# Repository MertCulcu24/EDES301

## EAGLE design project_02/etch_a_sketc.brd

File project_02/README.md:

# Etch-a-Sketch PCB Project

## Project Overview
This project is a PCB design for an Etch-a-Sketch game using the PocketBeagle as the main processor. The design includes a custom PCB that connects the PocketBeagle to various components to create a functional electronic version of the classic Etch-a-Sketch toy.

## Features
- **SPI Display**: Shows the drawing created by the user
- **Dual Potentiometers**: Control horizontal and vertical movement
- **Push Buttons**: Reset the drawing and change colors
- **RGB LEDs**: Indicate the currently selected color
- **USB Port**: Provides power and potential connectivity for expansion

## Repository Structure
```
project_02/
├── EAGLE/
│   ├── etch_a_sketch.lbr  # Custom component library
│   ├── etch_a_sketch.sch  # Schematic design
│   └── etch_a_sketch.brd  # PCB layout
├── docs/
│   ├── mechanical_diagram.pdf  # Physical layout diagram
│   ├── top_layer_screenshot.png  # PCB top layer view
│   └── bottom_layer_screenshot.png  # PCB bottom layer view
├── MFG/
│   ├── etch_a_sketch_bom.csv  # Bill of Materials
│   └── [gerber files]  # Manufacturing files for PCB production
└── README.md 
```

## Design Specifications
- **Board Size**: 4" x 5" maximum
- **Layers**: 4-layer PCB design
- **Design Rules**:
  - Signal traces: 10 mil width / 10 mil spacing
  - Power/ground traces: 15 mil width / 15 mil spacing
  - Vias: 12 mil drill / 24 mil pad

## Component List
- PocketBeagle single-board computer
- 2.8" SPI TFT Display
- 2x 10kΩ potentiometers (for X and Y control)
- 2x push buttons (reset and color change)
- 3x LEDs (red, green, blue)
- USB connector
- Various resistors and supporting components

## How to Use
1. Assemble the PCB with all components listed in the BOM
2. Power the board via USB
3. Press the color button to change drawing color
4. Press the reset button to clear the screen

## Manufacturing
This PCB was designed to be manufactured using standard PCB fabrication processes. The Gerber files in the MFG folder can be sent to any PCB manufacturer for production.

## Course Information
- **Course**: EDES301 - PCB Design
- **Due Date**: May 6, 2025
- **Instructor**: Dr. Welsh

## License
All design files are provided for educational purposes.

## Contact
mc205@rice.edu

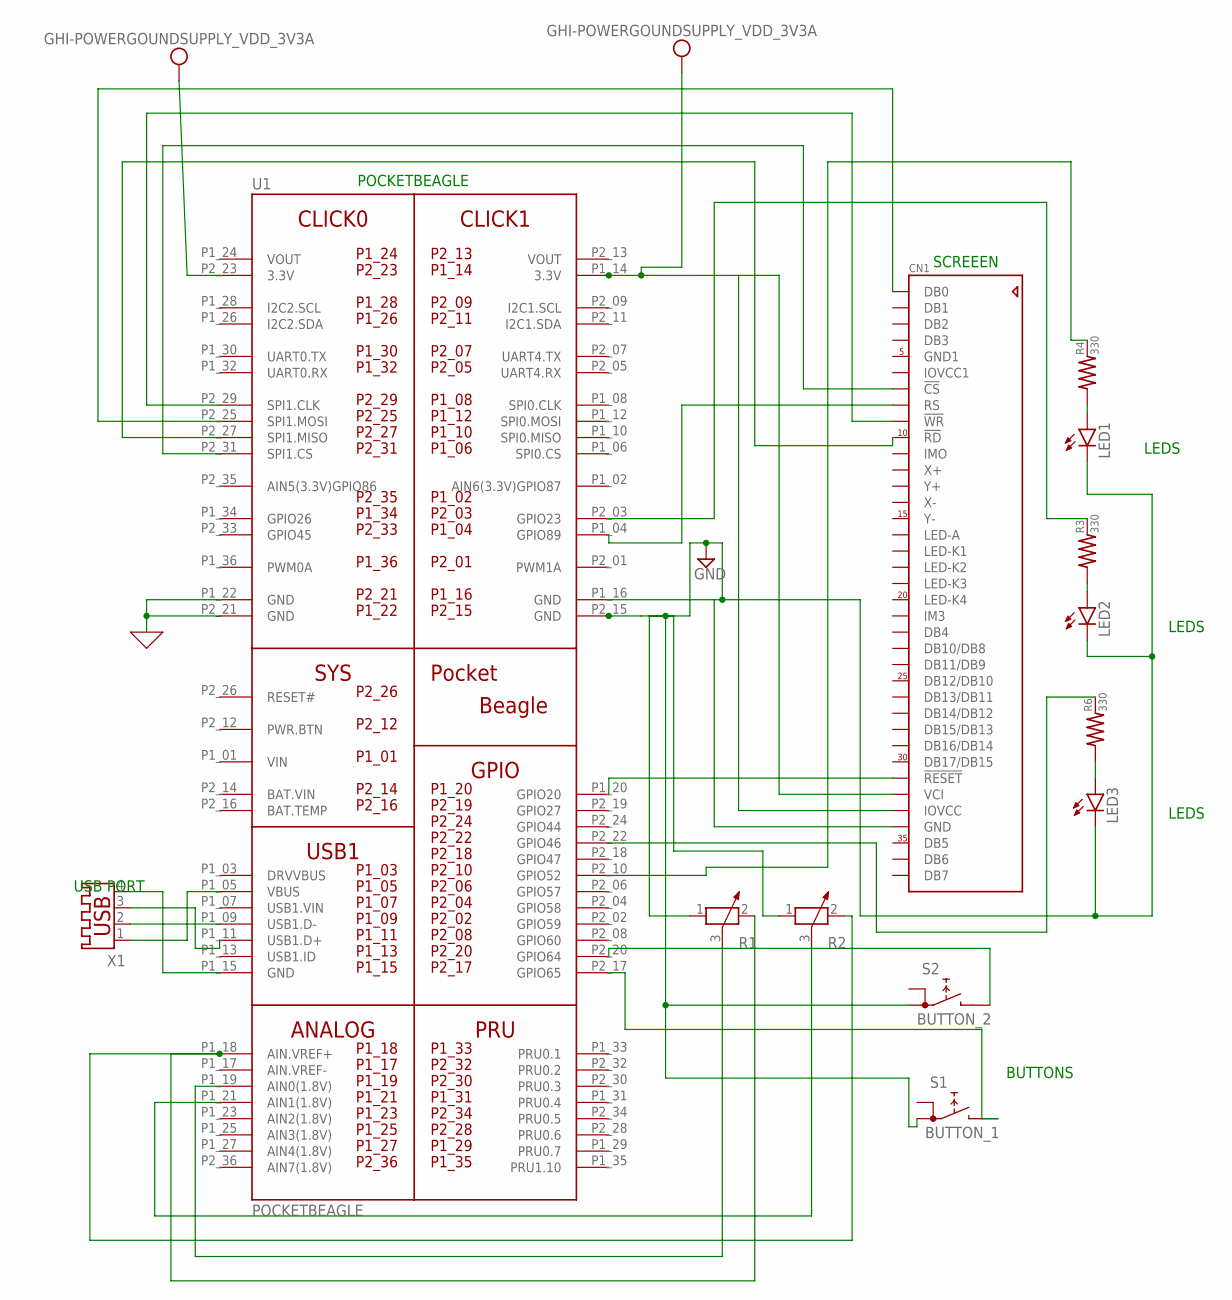
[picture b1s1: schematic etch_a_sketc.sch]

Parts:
CN1: ADAFRUIT_ILI9325_LCD1.0MM; ADAFRUIT_ILI9325_28INCH_TS
LED1: LED_BLUE5MM; LED5MM
LED2: LED_GREEN5MM; LED5MM
LED3: LED_RED5MM; LED5MM
R1: POTENTIOMETER_PT-10; PT-10
R2: POTENTIOMETER_2PT-10; PT-10
R3, R4, R6: 330; GHI-BASICCOMPONENTS_0402
S1: BUTTON_1; RDT1034
S2: BUTTON_2; RDT1034
U1: POCKETBEAGLE
X1: USB_CONNECTOR; USB-A003

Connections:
0: U1.P1_22 (GND), U1.P2_21 (GND)
BAT.VIN: U1.P2_14 (BAT.VIN)
GND: CN1.34 (GND), LED1.K (C), LED2.K (C), LED3.K (C), R1.1, R2.1, S1.A1, S2.A1, U1.P1_16 (GND), U1.P2_15 (GND)
GND1: CN1.5 (GND1)
IOVCC1: CN1.6 (IOVCC1)
unnamed: CN1.7 (!CS), U1.P2_31 (SPI1.CS)
unnamed: CN1.8 (RS), U1.P1_04 (GPIO89)
unnamed: CN1.9 (!WR), U1.P2_29 (SPI1.CLK)
unnamed: CN1.10 (!RD), U1.P2_27 (SPI1.MISO)
unnamed: CN1.1 (DB0), U1.P2_25 (SPI1.MOSI)
unnamed: CN1.31 (!RESET), U1.P1_20 (GPIO20)
unnamed: U1.P1_09 (USB1.D-), X1.2
unnamed: R1.2, R2.2, U1.P1_18 (AIN.VREF+)
unnamed: R1.3, U1.P1_19 (AIN0(1.8V))
unnamed: R2.3, U1.P1_21 (AIN1(1.8V))
unnamed: LED1.A, R4.1
unnamed: S2.B, U1.P2_20 (GPIO64)
unnamed: S1.B, U1.P2_17 (GPIO65)
unnamed: LED2.A, R3.1
unnamed: LED3.A, R6.1
unnamed: U1.P1_05 (VBUS), X1.1
unnamed: U1.P1_11 (USB1.D+), X1.3
unnamed: U1.P1_15 (GND), X1.4
unnamed: R6.2, U1.P2_22 (GPIO46)
unnamed: R3.2, U1.P2_03 (GPIO23)
unnamed: R4.2, U1.P2_10 (GPIO52)
VDD_3V3A: CN1.32 (VCI), CN1.33 (IOVCC), U1.P1_14 (3.3V), U1.P2_23 (3.3V)
VIN: U1.P1_01 (VIN)
VOUT: U1.P1_24 (VOUT), U1.P2_13 (VOUT)

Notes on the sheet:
POCKETBEAGLE
SCREEEN
USB PORT
BUTTONS
LEDS

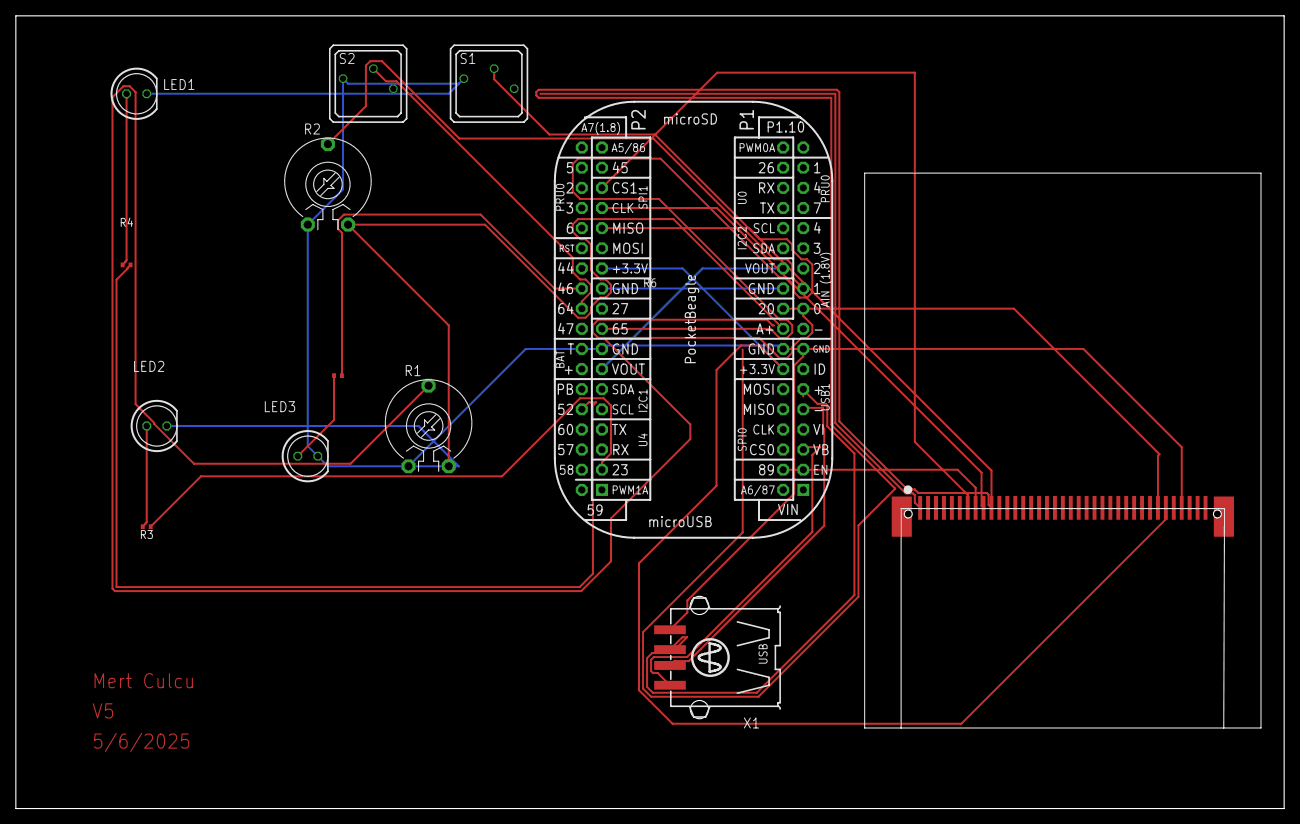
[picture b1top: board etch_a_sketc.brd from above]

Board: 4 copper layers, 160.0 x 100.0 mm, 13 parts (0 on the bottom side), 25 nets.

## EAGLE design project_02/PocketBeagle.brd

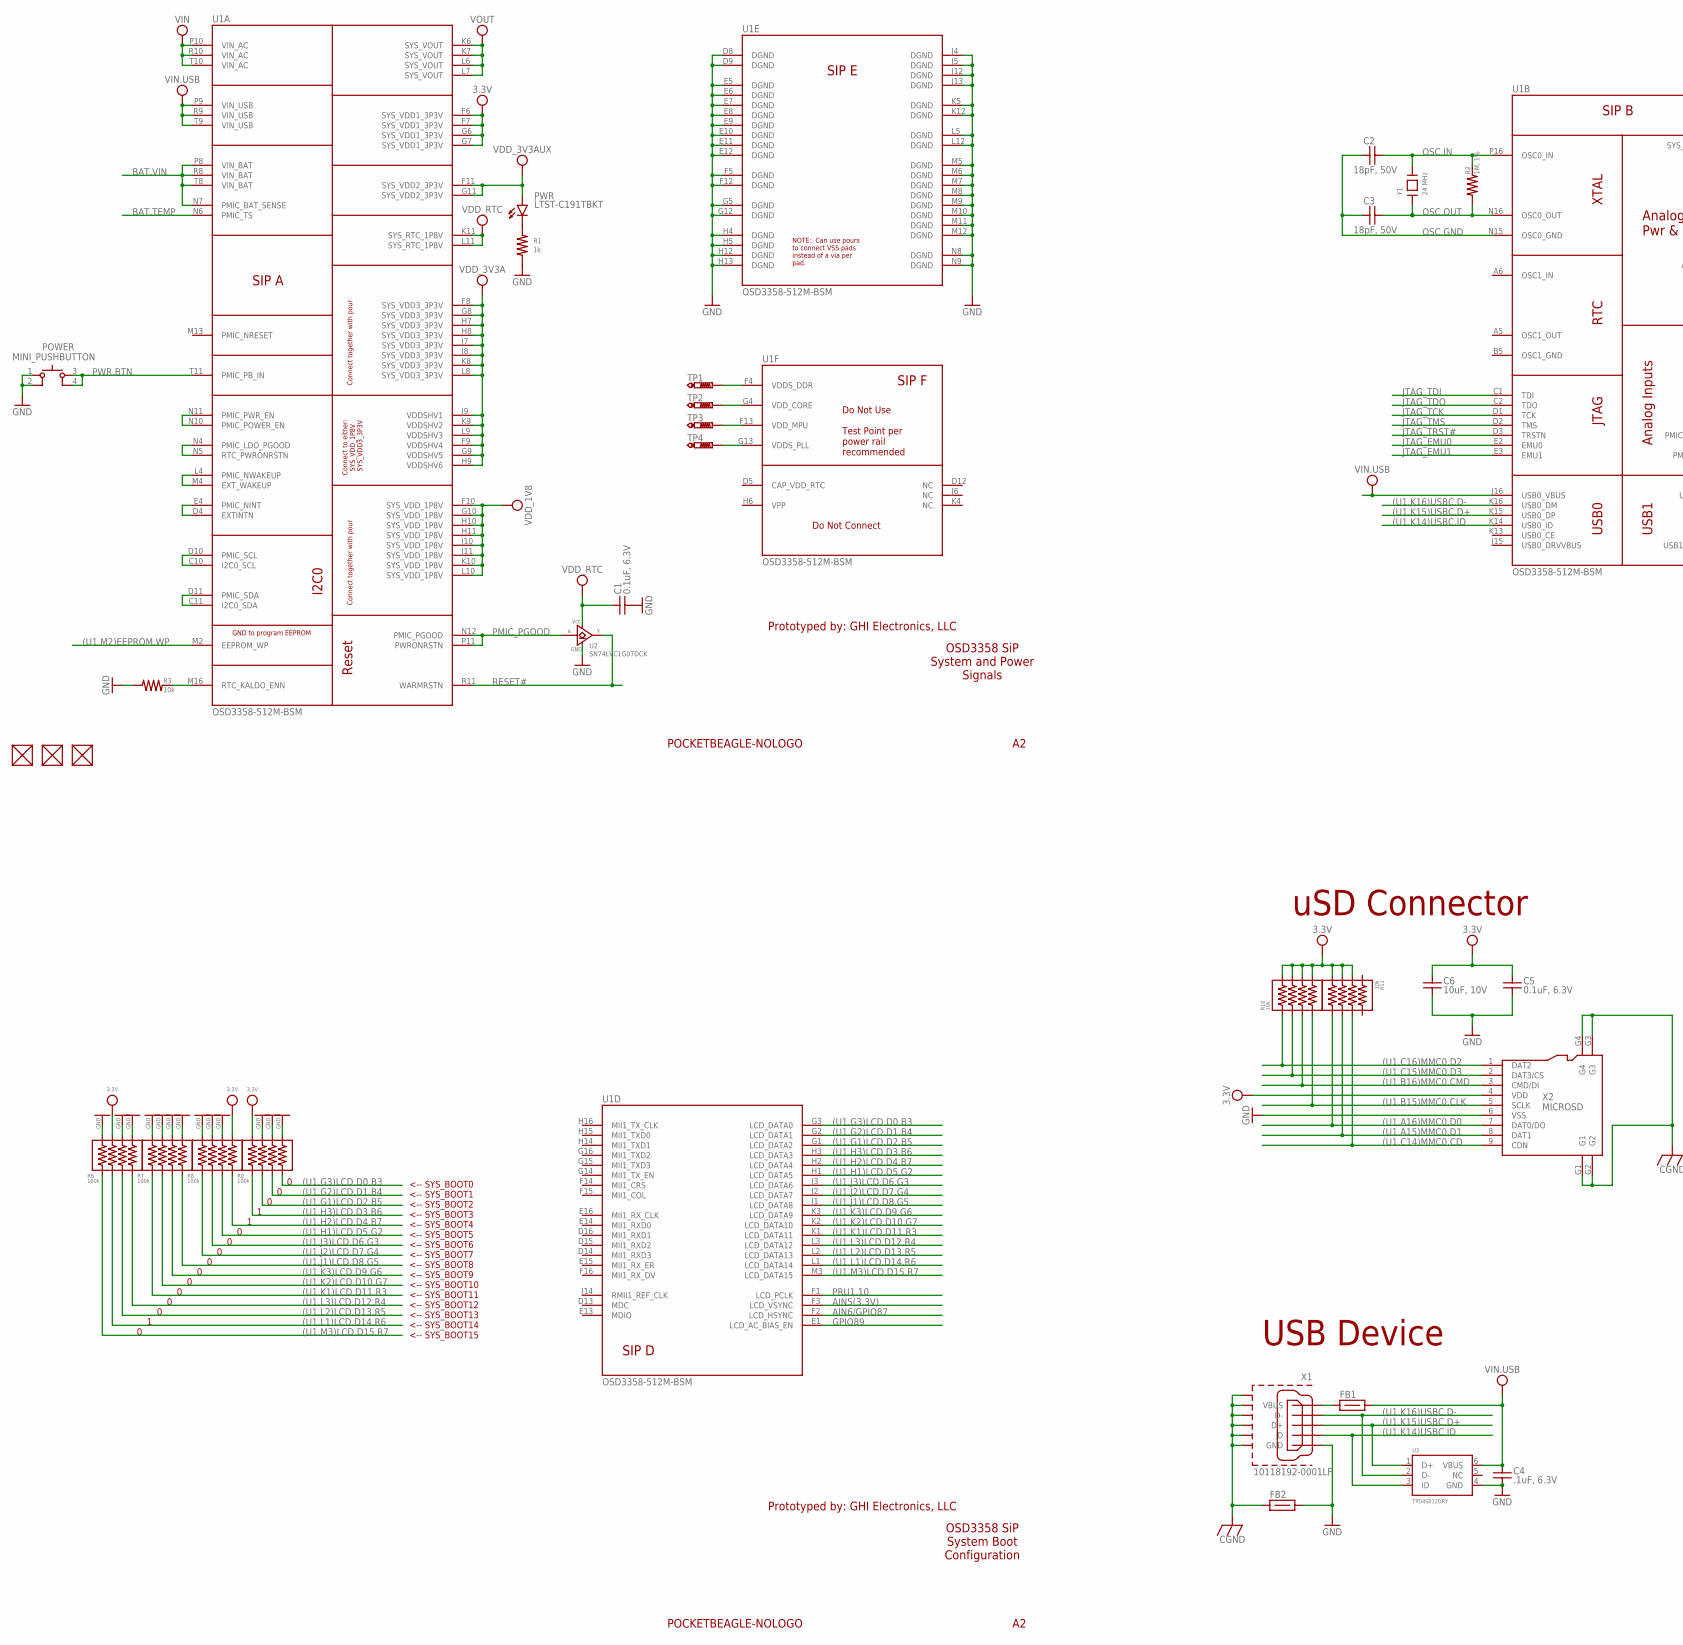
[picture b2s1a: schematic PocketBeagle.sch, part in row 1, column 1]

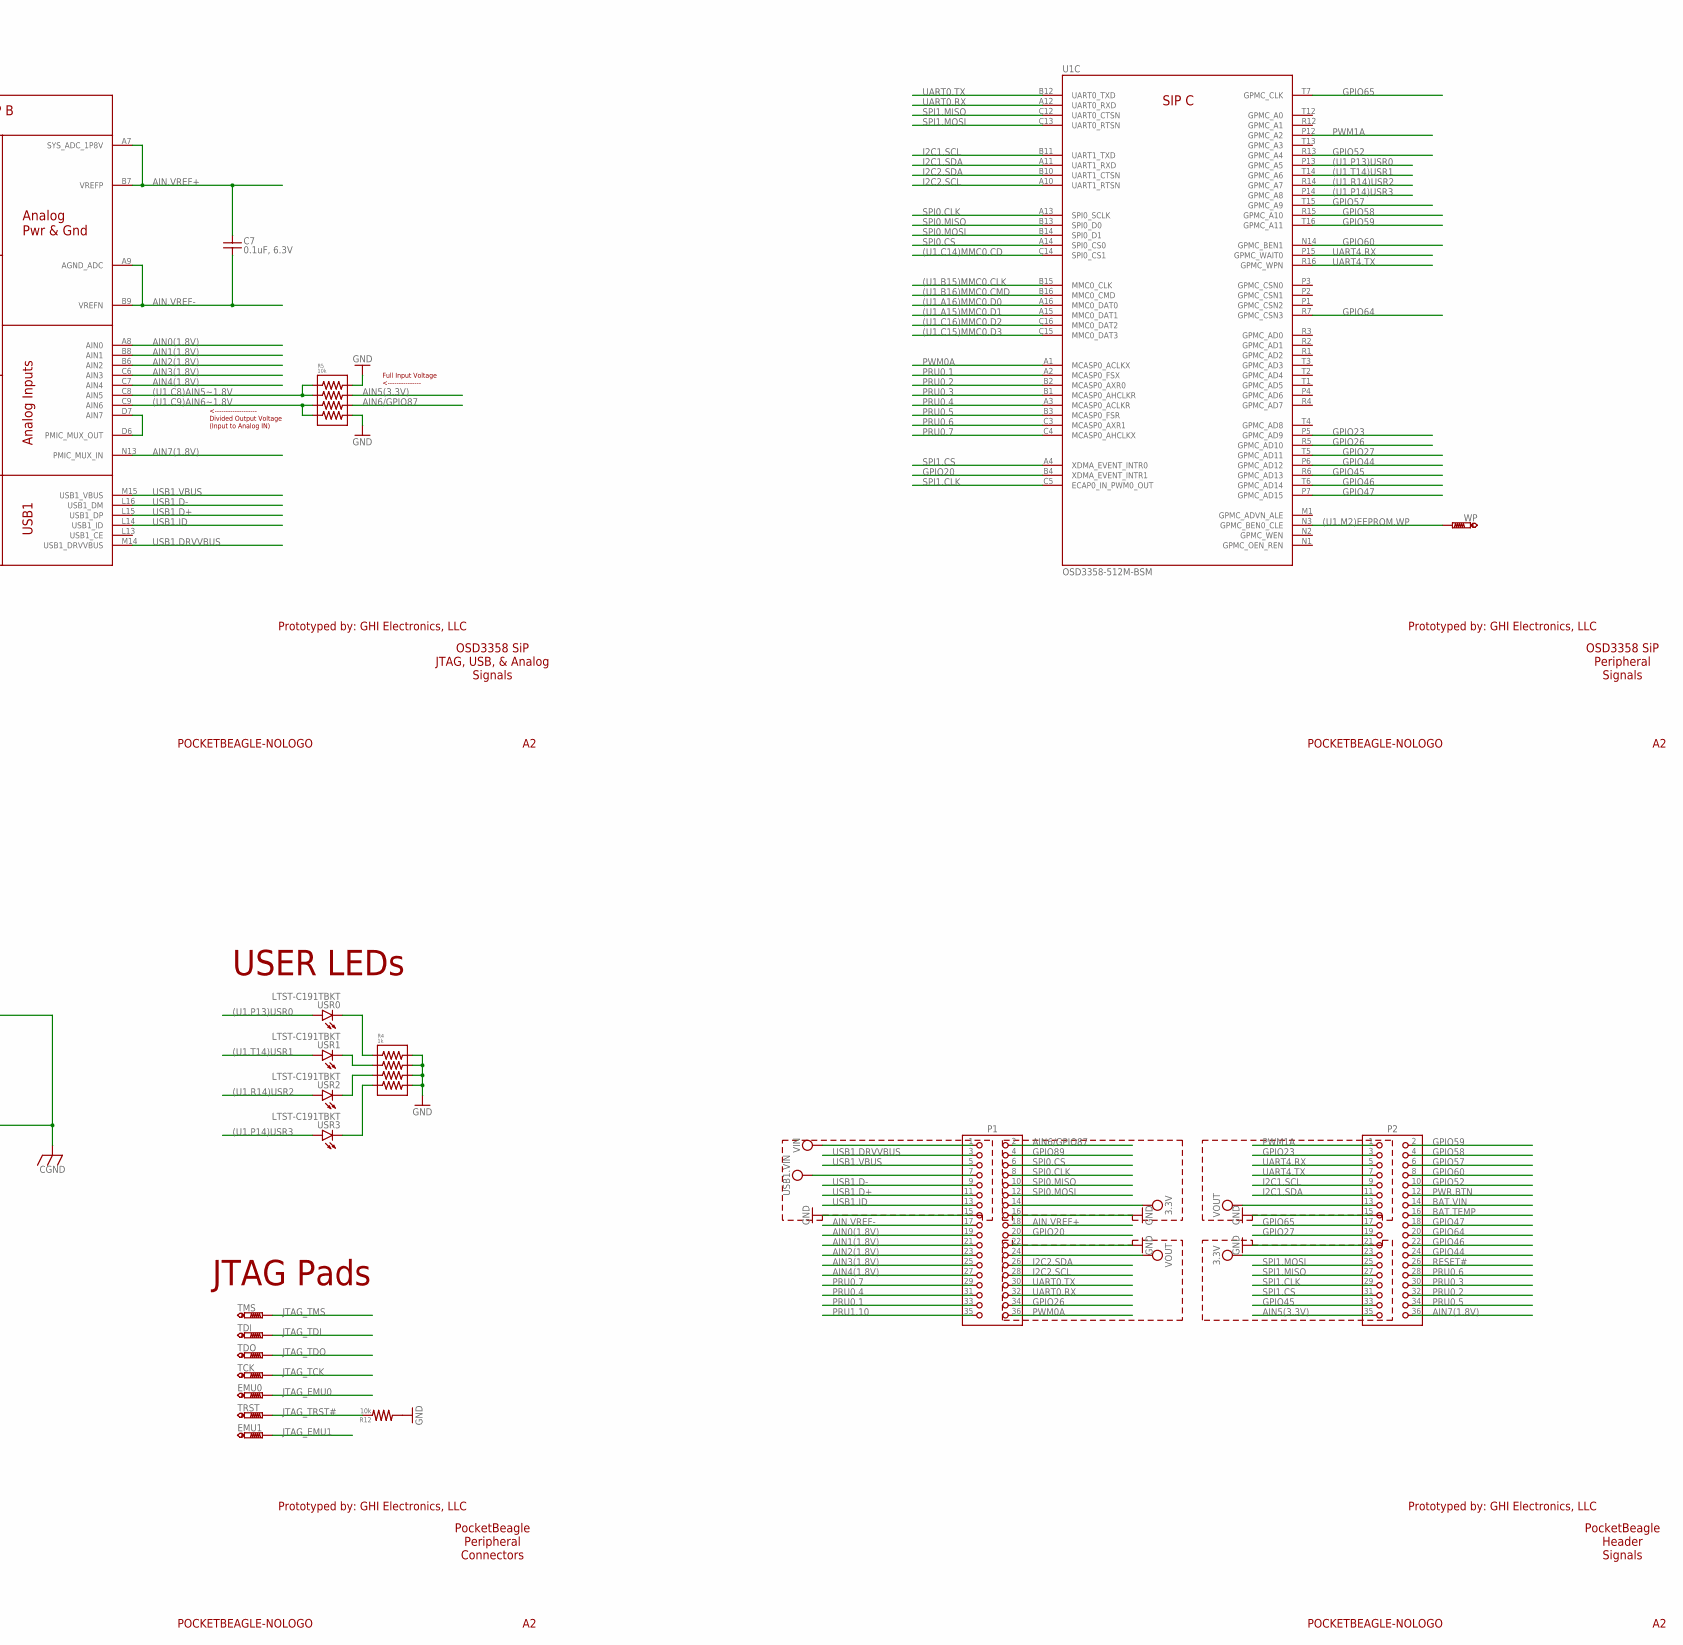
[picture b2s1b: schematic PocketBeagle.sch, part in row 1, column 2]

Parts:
C1, C5, C7: 0.1uF, 6.3V; 0402
C2, C3: 18pF, 50V; 0402
C4: .1uF, 6.3V; 0402
C6: 10uF, 10V; 0603
EMU0, EMU1: PTR1B1,27; B1,27
FB1, FB2: FB-(INCH)-0603; 0603
FUD1, FUD2, FUD3: FIDUCIAL; FIDUCIAL_40MIL
P1, P2: 2X18-(INCH)-0.1-TH-(35MIL-DIA)-W/O-SILK; TH-2X18-(35MIL-DIA)-W/O-SILK
POWER: MINI_PUSHBUTTON
PWR: LTST-C191TBKT; 0603-LED
R1: 1k; 0402
R2: 1M, 1%; 0402
R3, R12: 10k; 0402
R4: 1k; RN0804
R5, R10, R11: 10k; RN0804
R6, R7, R8, R9: 100k; RN0804
TCK: PTR1B1,27; B1,27
TDI: PTR1B1,27; B1,27
TDO: PTR1B1,27; B1,27
TMS: PTR1B1,27; B1,27
TP1, TP2, TP3, TP4: PTR1B1,27; B1,27
TRST: PTR1B1,27; B1,27
U1: OSD3358-512M-BSM; OSD335X-BGA-256
U2: SN74LVC1G07DCK; SC70(TI-DCK)
U3: TPD4S012DRY; SON-6(TI)-DRY
USR0, USR1, USR2, USR3: LTST-C191TBKT; 0603-LED
WP: PTR1B1,27; B1,27
X1: 10118192-0001LF; 10118192-0001LF(MICRO-USB-B-AMPHENOL-FCI)
X2: MICROSD
Y1: 24 MHz; CRYSTAL_5X3.2MM

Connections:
3.3V: C5.1, C6.1, P1.14, P2.23, R6.7, R8.5, R9.4, R10.5, R10.6, R10.7, R10.8, R11.2, R11.3, R11.4, U1.F6 (SYS_VDD1_3P3V), U1.F7 (SYS_VDD1_3P3V), U1.G6 (SYS_VDD1_3P3V), U1.G7 (SYS_VDD1_3P3V), X2.4 (VDD)
(U1.A15)MMC0.D1: R11.6, U1.A15 (MMC0_DAT1), X2.8 (DAT1)
(U1.A16)MMC0.D0: R11.5, U1.A16 (MMC0_DAT0), X2.7 (DAT0/DO)
(U1.B15)MMC0.CLK: R10.4, U1.B15 (MMC0_CLK), X2.5 (SCLK)
(U1.B16)MMC0.CMD: R10.3, U1.B16 (MMC0_CMD), X2.3 (CMD/DI)
(U1.C8)AIN5~1.8V: R5.1, R5.2, U1.C8 (AIN5)
(U1.C9)AIN6~1.8V: R5.3, R5.4, U1.C9 (AIN6)
(U1.C14)MMC0.CD: R11.7, U1.C14 (SPI0_CS1), X2.9 (CDN)
(U1.C15)MMC0.D3: R10.2, U1.C15 (MMC0_DAT3), X2.2 (DAT3/CS)
(U1.C16)MMC0.D2: R10.1, U1.C16 (MMC0_DAT2), X2.1 (DAT2)
(U1.G1)LCD.D2.B5: R9.6, U1.G1 (LCD_DATA2)
(U1.G2)LCD.D1.B4: R9.7, U1.G2 (LCD_DATA1)
(U1.G3)LCD.D0.B3: R9.8, U1.G3 (LCD_DATA0)
(U1.H1)LCD.D5.G2: R8.3, U1.H1 (LCD_DATA5)
(U1.H2)LCD.D4.B7: R8.4, U1.H2 (LCD_DATA4)
(U1.H3)LCD.D3.B6: R9.5, U1.H3 (LCD_DATA3)
(U1.J1)LCD.D8.G5: R7.4, U1.J1 (LCD_DATA8)
(U1.J2)LCD.D7.G4: R8.1, U1.J2 (LCD_DATA7)
(U1.J3)LCD.D6.G3: R8.2, U1.J3 (LCD_DATA6)
(U1.K1)LCD.D11.R3: R7.1, U1.K1 (LCD_DATA11)
(U1.K2)LCD.D10.G7: R7.2, U1.K2 (LCD_DATA10)
(U1.K3)LCD.D9.G6: R7.3, U1.K3 (LCD_DATA9)
(U1.K14)USBC.ID: U1.K14 (USB0_ID), U3.3 (ID), X1.ID
(U1.K15)USBC.D+: U1.K15 (USB0_DP), U3.1 (D+), X1.D+
(U1.K16)USBC.D-: U1.K16 (USB0_DM), U3.2 (D-), X1.D-
(U1.L1)LCD.D14.R6: R6.2, U1.L1 (LCD_DATA14)
(U1.L2)LCD.D13.R5: R6.3, U1.L2 (LCD_DATA13)
(U1.L3)LCD.D12.R4: R6.4, U1.L3 (LCD_DATA12)
(U1.M2)EEPROM.WP: U1.M2 (EEPROM_WP), U1.N3 (GPMC_BEN0_CLE), WP.TP
(U1.M3)LCD.D15.R7: R6.1, U1.M3 (LCD_DATA15)
(U1.P13)USR0: U1.P13 (GPMC_A5), USR0.A
(U1.P14)USR3: U1.P14 (GPMC_A8), USR3.A
(U1.R14)USR2: U1.R14 (GPMC_A7), USR2.A
(U1.T14)USR1: U1.T14 (GPMC_A6), USR1.A
AIN0(1.8V): P1.19, U1.A8 (AIN0)
AIN1(1.8V): P1.21, U1.B8 (AIN1)
AIN2(1.8V): P1.23, U1.B6 (AIN2)
AIN3(1.8V): P1.25, U1.C6 (AIN3)
AIN4(1.8V): P1.27, U1.C7 (AIN4)
AIN5(3.3V): P2.35, R5.7, U1.F3 (LCD_VSYNC)
AIN6/GPIO87: P1.2, R5.6, U1.F2 (LCD_HSYNC)
AIN7(1.8V): P2.36, U1.N13 (PMIC_MUX_IN)
AIN.VREF+: C7.1, P1.18, U1.A7 (SYS_ADC_1P8V), U1.B7 (VREFP)
AIN.VREF-: C7.2, P1.17, U1.A9 (AGND_ADC), U1.B9 (VREFN)
BAT.TEMP: P2.16, U1.N6 (PMIC_TS)
BAT.VIN: P2.14, U1.N7 (PMIC_BAT_SENSE), U1.P8 (VIN_BAT), U1.R8 (VIN_BAT), U1.T8 (VIN_BAT)
CGND: FB2.1, X1.CGND1 (SGND1), X1.CGND2 (SGND2), X1.CGND3 (SGND3), X1.CGND4 (SGND4), X1.CGND5 (SGND5), X1.CGND6 (SGND6), X2.G1, X2.G2, X2.G3, X2.G4
GND: C1.2, C4.2, C5.2, C6.2, FB2.2, P1.15, P1.16, P1.22, P2.15, P2.21, POWER.1, POWER.2, R1.1, R3.1, R4.5, R4.6, R4.7, R4.8, R5.5, R5.8, R6.5, R6.6, R6.8, R7.5, R7.6, R7.7, R7.8, R8.6, R8.7, R8.8, R9.1, R9.2, R9.3, R12.1, U1.D8 (DGND), U1.D9 (DGND), U1.E5 (DGND), U1.E6 (DGND), U1.E7 (DGND), U1.E8 (DGND), U1.E9 (DGND), U1.E10 (DGND), U1.E11 (DGND), U1.E12 (DGND), U1.F5 (DGND), U1.F12 (DGND), U1.G5 (DGND), U1.G12 (DGND), U1.H4 (DGND), U1.H5 (DGND), U1.H12 (DGND), U1.H13 (DGND), U1.J4 (DGND), U1.J5 (DGND), U1.J12 (DGND), U1.J13 (DGND), U1.K5 (DGND), U1.K12 (DGND), U1.L5 (DGND), U1.L12 (DGND), U1.M5 (DGND), U1.M6 (DGND), U1.M7 (DGND), U1.M8 (DGND), U1.M9 (DGND), U1.M10 (DGND), U1.M11 (DGND), U1.M12 (DGND), U1.N8 (DGND), U1.N9 (DGND), U2.3 (GND), U3.4 (GND), X1.GND, X2.6 (VSS)
GPIO20: P1.20, U1.B4 (XDMA_EVENT_INTR1)
GPIO23: P2.3, U1.P5 (GPMC_AD9)
GPIO26: P1.34, U1.R5 (GPMC_AD10)
GPIO27: P2.19, U1.T5 (GPMC_AD11)
GPIO44: P2.24, U1.P6 (GPMC_AD12)
GPIO45: P2.33, U1.R6 (GPMC_AD13)
GPIO46: P2.22, U1.T6 (GPMC_AD14)
GPIO47: P2.18, U1.P7 (GPMC_AD15)
GPIO52: P2.10, U1.R13 (GPMC_A4)
GPIO57: P2.6, U1.T15 (GPMC_A9)
GPIO58: P2.4, U1.R15 (GPMC_A10)
GPIO59: P2.2, U1.T16 (GPMC_A11)
GPIO60: P2.8, U1.N14 (GPMC_BEN1)
GPIO64: P2.20, U1.R7 (GPMC_CSN3)
GPIO65: P2.17, U1.T7 (GPMC_CLK)
GPIO89: P1.4, U1.E1 (LCD_AC_BIAS_EN)
I2C1.SCL: P2.9, U1.B11 (UART1_TXD)
I2C1.SDA: P2.11, U1.A11 (UART1_RXD)
I2C2.SCL: P1.28, U1.A10 (UART1_RTSN)
I2C2.SDA: P1.26, U1.B10 (UART1_CTSN)
JTAG_EMU0: EMU0.TP, U1.E2 (EMU0)
JTAG_EMU1: EMU1.TP, U1.E3 (EMU1)
JTAG_TCK: TCK.TP, U1.D1 (TCK)
JTAG_TDI: TDI.TP, U1.C1 (TDI)
JTAG_TDO: TDO.TP, U1.C2 (TDO)
JTAG_TMS: TMS.TP, U1.D2 (TMS)
JTAG_TRST#: R12.2, TRST.TP, U1.D3 (TRSTN)
unnamed: R4.3, USR2.K
unnamed: R4.4, USR3.K
unnamed: PWR.K, R1.2
unnamed: R4.2, USR1.K
unnamed: R4.1, USR0.K
unnamed: TP1.TP, U1.F4 (VDDS_DDR)
unnamed: TP2.TP, U1.G4 (VDD_CORE)
unnamed: TP3.TP, U1.F13 (VDD_MPU)
unnamed: TP4.TP, U1.G13 (VDDS_PLL)
unnamed: U1.D6 (PMIC_MUX_OUT), U1.D7 (AIN7)
unnamed: R3.2, U1.M16 (RTC_KALDO_ENN)
unnamed: U1.N4 (PMIC_LDO_PGOOD), U1.N5 (RTC_PWRONRSTN)
unnamed: U1.L4 (PMIC_NWAKEUP), U1.M4 (EXT_WAKEUP)
unnamed: U1.D4 (EXTINTN), U1.E4 (PMIC_NINT)
unnamed: U1.N10 (PMIC_POWER_EN), U1.N11 (PMIC_PWR_EN)
unnamed: U1.C11 (I2C0_SDA), U1.D11 (PMIC_SDA)
unnamed: U1.C10 (I2C0_SCL), U1.D10 (PMIC_SCL)
OSC.GND: C2.1, C3.1, U1.N15 (OSC0_GND)
OSC.IN: C2.2, R2.2, U1.P16 (OSC0_IN), Y1.2
OSC.OUT: C3.2, R2.1, U1.N16 (OSC0_OUT), Y1.1
PMIC_PGOOD: U1.N12 (PMIC_PGOOD), U1.P11 (PWRONRSTN), U2.2 (A)
PRU0.1: P1.33, U1.A2 (MCASP0_FSX)
PRU0.2: P2.32, U1.B2 (MCASP0_AXR0)
PRU0.3: P2.30, U1.B1 (MCASP0_AHCLKR)
PRU0.4: P1.31, U1.A3 (MCASP0_ACLKR)
PRU0.5: P2.34, U1.B3 (MCASP0_FSR)
PRU0.6: P2.28, U1.C3 (MCASP0_AXR1)
PRU0.7: P1.29, U1.C4 (MCASP0_AHCLKX)
PRU1.10: P1.35, U1.F1 (LCD_PCLK)
PWM0A: P1.36, U1.A1 (MCASP0_ACLKX)
PWM1A: P2.1, U1.P12 (GPMC_A2)
PWR.BTN: P2.12, POWER.3, POWER.4, U1.T11 (PMIC_PB_IN)
RESET#: P2.26, U1.R11 (WARMRSTN), U2.4 (Y)
SPI0.CLK: P1.8, U1.A13 (SPI0_SCLK)
SPI0.CS: P1.6, U1.A14 (SPI0_CS0)
SPI0.MISO: P1.10, U1.B13 (SPI0_D0)
SPI0.MOSI: P1.12, U1.B14 (SPI0_D1)
SPI1.CLK: P2.29, U1.C5 (ECAP0_IN_PWM0_OUT)
SPI1.CS: P2.31, U1.A4 (XDMA_EVENT_INTR0)
SPI1.MISO: P2.27, U1.C12 (UART0_CTSN)
SPI1.MOSI: P2.25, U1.C13 (UART0_RTSN)
UART0.RX: P1.32, U1.A12 (UART0_RXD)
UART0.TX: P1.30, U1.B12 (UART0_TXD)
UART4.RX: P2.5, U1.P15 (GPMC_WAIT0)
UART4.TX: P2.7, U1.R16 (GPMC_WPN)
USB1.D+: P1.11, U1.L15 (USB1_DP)
USB1.D-: P1.9, U1.L16 (USB1_DM)
USB1.DRVVBUS: P1.3, U1.M14 (USB1_DRVVBUS)
USB1.ID: P1.13, U1.L14 (USB1_ID)
USB1.VBUS: P1.5, U1.M15 (USB1_VBUS)
VBUS.RAW: FB1.1, X1.VBUS
VDD_1V8: U1.F10 (SYS_VDD_1P8V), U1.G10 (SYS_VDD_1P8V), U1.H10 (SYS_VDD_1P8V), U1.H11 (SYS_VDD_1P8V), U1.J10 (SYS_VDD_1P8V), U1.J11 (SYS_VDD_1P8V), U1.K10 (SYS_VDD_1P8V), U1.L10 (SYS_VDD_1P8V)
VDD_3V3A: U1.F8 (SYS_VDD3_3P3V), U1.F9 (VDDSHV4), U1.G8 (SYS_VDD3_3P3V), U1.G9 (VDDSHV5), U1.H7 (SYS_VDD3_3P3V), U1.H8 (SYS_VDD3_3P3V), U1.H9 (VDDSHV6), U1.J7 (SYS_VDD3_3P3V), U1.J8 (SYS_VDD3_3P3V), U1.J9 (VDDSHV1), U1.K8 (SYS_VDD3_3P3V), U1.K9 (VDDSHV2), U1.L8 (SYS_VDD3_3P3V), U1.L9 (VDDSHV3)
VDD_3V3AUX: PWR.A, U1.F11 (SYS_VDD2_3P3V), U1.G11 (SYS_VDD2_3P3V)
VDD_RTC: C1.1, U1.K11 (SYS_RTC_1P8V), U1.L11 (SYS_RTC_1P8V), U2.5 (VCC)
VIN: P1.1, U1.P10 (VIN_AC), U1.R10 (VIN_AC), U1.T10 (VIN_AC)
VIN.USB: C4.1, FB1.2, P1.7, U1.J16 (USB0_VBUS), U1.P9 (VIN_USB), U1.R9 (VIN_USB), U1.T9 (VIN_USB), U3.6 (VBUS)
VOUT: P1.24, P2.13, U1.K6 (SYS_VOUT), U1.K7 (SYS_VOUT), U1.L6 (SYS_VOUT), U1.L7 (SYS_VOUT)

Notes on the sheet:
<-- SYS_BOOT0 <-- SYS_BOOT1 <-- SYS_BOOT2 <-- SYS_BOOT3 <-- SYS_BOOT4 <-- SYS_BOOT5 <-- SYS_BOOT6 <-- SYS_BOOT7 <-- SYS_BOOT8 <-- SYS_BOOT9 <-- SYS_BOOT10 <-- SYS_BOOT11 <-- SYS_BOOT12 <-- SYS_BOOT13 <-- SYS_BOOT14 <-- SYS_BOOT15
USB Device
USER LEDs
uSD Connector
OSD3358 SiP System and Power Signals
Prototyped by: GHI Electronics, LLC
POCKETBEAGLE-NOLOGO
Full Input Voltage <---------------
<------------------- Divided Output Voltage (Input to Analog IN)
OSD3358 SiP JTAG, USB, & Analog Signals
OSD3358 SiP Peripheral Signals
OSD3358 SiP System Boot Configuration
PocketBeagle Peripheral Connectors
PocketBeagle Header Signals
JTAG Pads

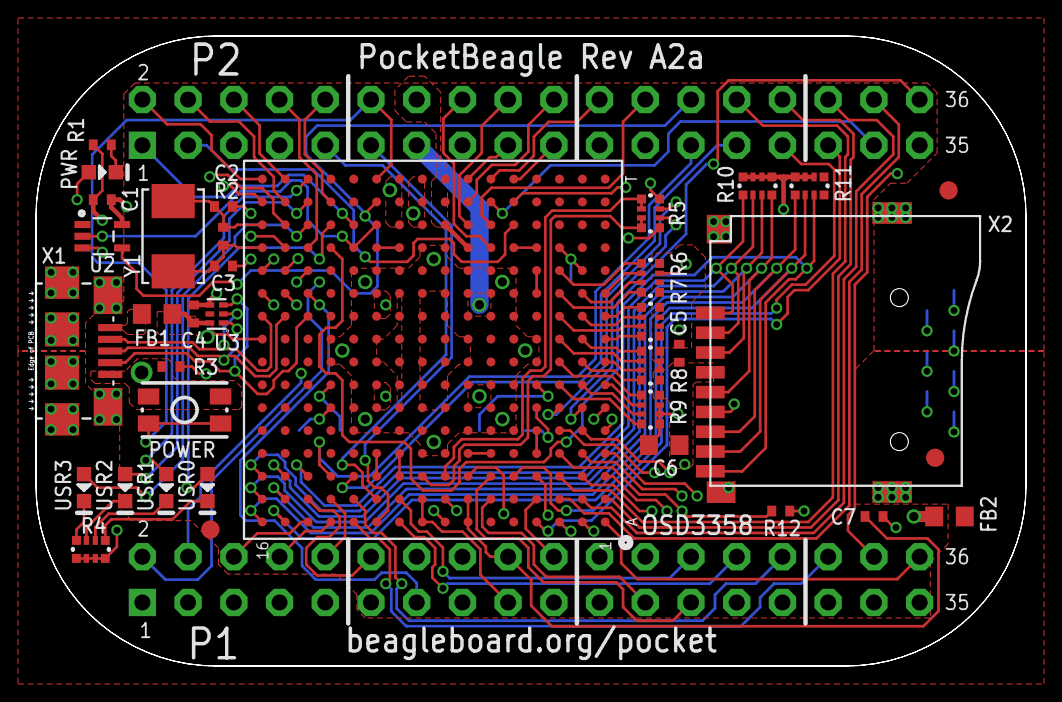
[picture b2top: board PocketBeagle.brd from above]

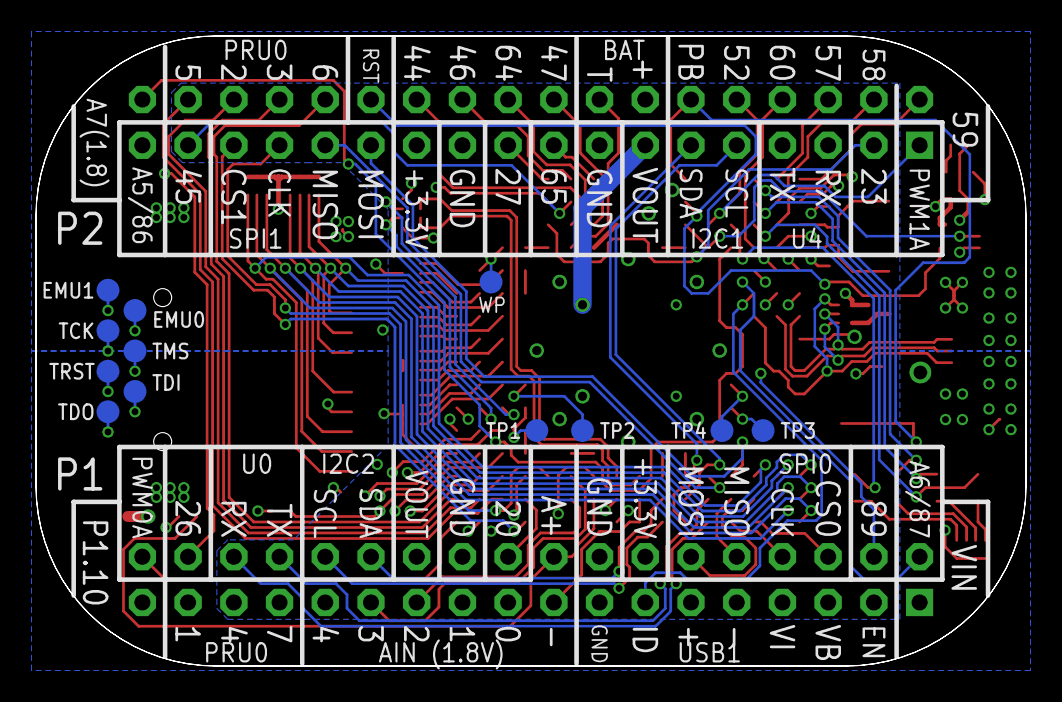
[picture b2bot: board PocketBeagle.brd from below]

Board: 4 copper layers, 55.0 x 35.0 mm, 50 parts (12 on the bottom side), 133 nets.

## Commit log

2025-02-14 Blinking Led
2025-05-05 EDES301 Assignments
2025-05-05 EDES301 Assigment
2025-05-05 EDES301 Assigments
2025-05-05 Remove submodule folders
2025-05-05 EDES 301 Assignments
2025-05-05 Project 1
2025-05-05 Remove top-level CNC_Mechanism and Checkers_Mechanism_Remote_Control folders
2025-05-05 Replace old README with new project overview
2025-05-05 ReadMe Update
2025-05-05 Presentation + Folder Name Change
2025-05-08 Initial commit: Etch-a-Sketch PCB project
2025-05-08 ReadMe
2025-05-09 PowerPoint and Frame Info
